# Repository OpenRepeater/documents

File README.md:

Welcome to the OpenRepeater Project.
=======

This is the main repository for the OpenRepeater Project where WIKIs and Issues live.

Please go to the OpenRepeater organization to see all the associated repositories with this project: https://github.com/OpenRepeater

PROJECT PAGE
https://Openrepeater.com

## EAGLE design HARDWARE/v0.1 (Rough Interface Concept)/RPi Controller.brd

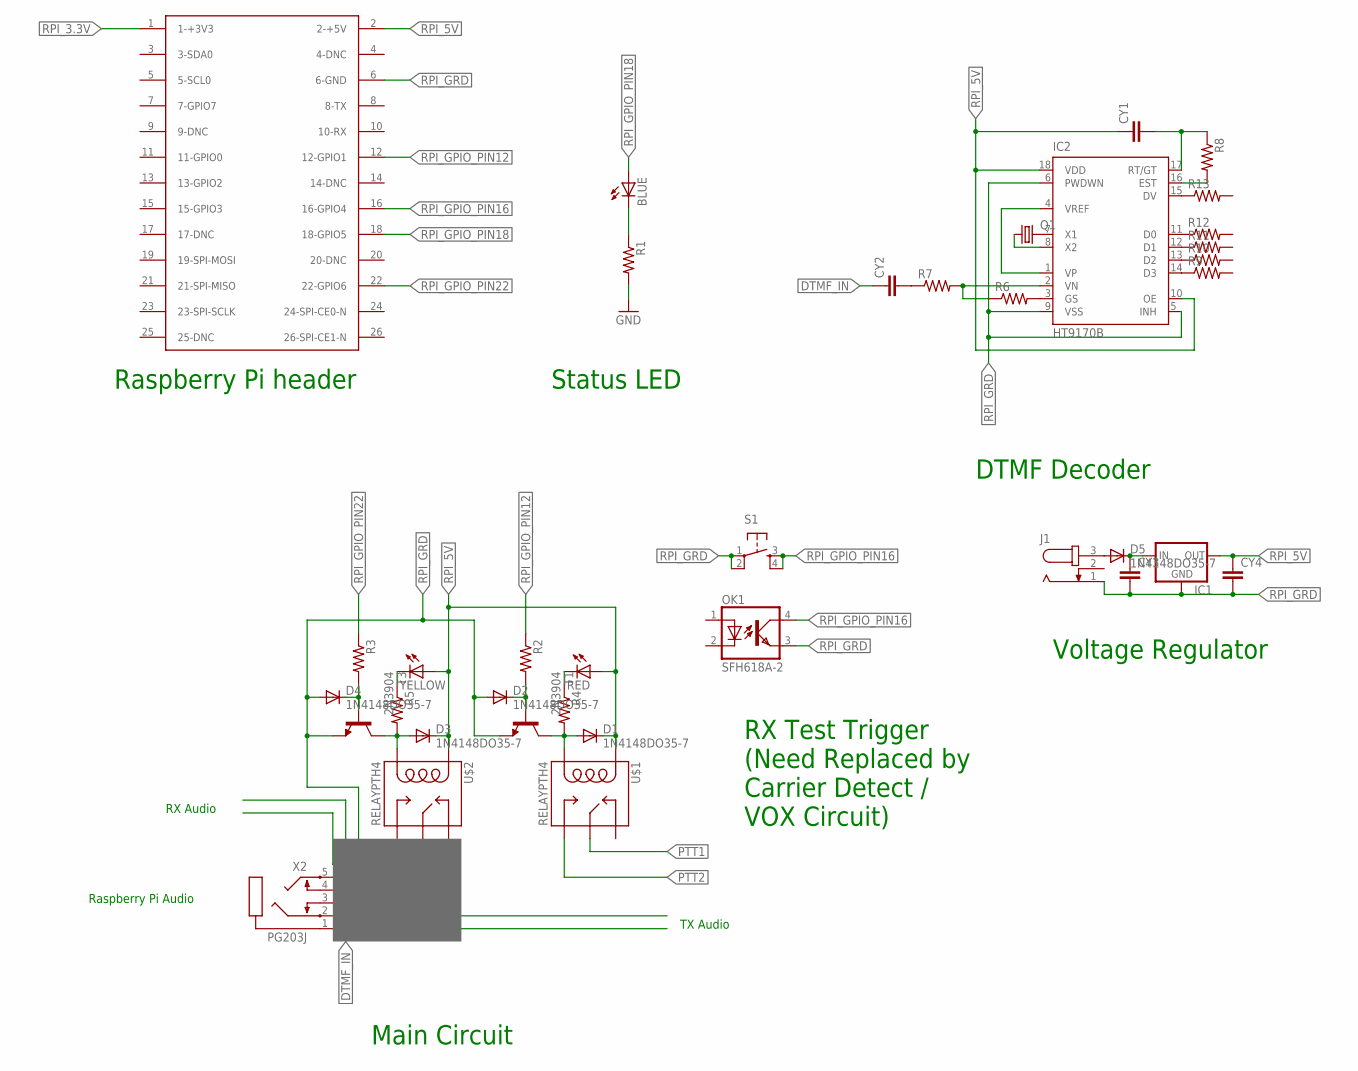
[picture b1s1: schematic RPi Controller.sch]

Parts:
BLUE: LED3MM
CY1, CY2, CY3, CY4: CYYC7B5; YC7B5
D1, D2, D3, D4, D5: 1N4148DO35-7; DO35-7
IC1: V_REG_78XX-TO-220; TO-220-ALT
IC2: HT9170B; DIL18
J1: JACK-PLUG0; SPC4077
OK1: SFH618A-2; DIP4
Q1: CRYSTALHC49U-V; HC49U-V
R1, R2, R3, R4, R5, R6, R7, R8, R9, R10, R11, R12, R13: R-US_0204/7; 0204/7
RED: LED3MM
S1: TAC_SWITCHPTH; TACTILE-PTH
T1, T3: 2N3904; TO92
U$1, U$2: RELAYPTH4; RELAY-JZC
X1: P1A; RASPBERRY-PI-HEADER
X2: PG203J
YELLOW: LED3MM

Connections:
DTMF_IN: CY2.1, U$2.4 (MAIN)
GND: R1.2
unnamed: BLUE.K (C), R1.1
unnamed: R4.1, RED.K (C)
unnamed: U$2.2 (NC), X2.5
unnamed: D2.C, R2.2, T1.2 (B)
unnamed: D1.A, R4.2, T1.1 (C), U$1.1 (COIL2)
unnamed: R5.1, YELLOW.K (C)
unnamed: IC2.7 (X1), Q1.2
unnamed: D4.C, R3.2, T3.2 (B)
unnamed: D3.A, R5.2, T3.1 (C), U$2.1 (COIL2)
unnamed: IC2.8 (X2), Q1.1
unnamed: IC2.14 (D3), R9.1
unnamed: IC2.2 (VN), R6.1, R7.2
unnamed: IC2.13 (D2), R10.1
unnamed: IC2.3 (GS), R6.2
unnamed: IC2.1 (VP), IC2.4 (VREF)
unnamed: IC2.12 (D1), R11.1
unnamed: IC2.11 (D0), R12.1
unnamed: IC2.15 (DV), R13.1
unnamed: CY3.1, D5.C, IC1.IN
unnamed: IC2.16 (EST), R8.2
unnamed: CY1.2, IC2.17 (RT/GT), R8.1
unnamed: CY2.2, R7.1
unnamed: D5.A, J1.3
PTT1: U$1.4 (MAIN)
PTT2: U$1.3 (NO)
RPI_3.3V: X1.1 (1-+3V3)
RPI_5V: CY1.1, CY4.1, D1.C, D3.C, IC1.OUT, IC2.10 (OE), IC2.18 (VDD), RED.A, U$1.5 (COIL1), U$2.5 (COIL1), X1.2 (2-+5V), YELLOW.A
RPI_GPIO_PIN12: R2.1, X1.12 (12-GPIO1)
RPI_GPIO_PIN16: OK1.4 (COL), S1.3, S1.4, X1.16 (16-GPIO4)
RPI_GPIO_PIN18: BLUE.A, X1.18 (18-GPIO5)
RPI_GPIO_PIN22: R3.1, X1.22 (22-GPIO6)
RPI_GRD: CY3.2, CY4.2, D2.A, D4.A, IC1.GND, IC2.5 (INH), IC2.6 (PWDWN), IC2.9 (VSS), J1.1, OK1.3 (EMIT), S1.1, S1.2, T1.3 (E), T3.3 (E), X1.6 (6-GND), X2.1

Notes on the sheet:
Raspberry Pi header
Status LED
Raspberry Pi Audio
RX Audio
TX Audio
DTMF Decoder
Voltage Regulator
Main Circuit
RX Test Trigger (Need Replaced by Carrier Detect / VOX Circuit)

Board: 2 copper layers, 37 parts (0 on the bottom side), 30 nets, no tracks yet.

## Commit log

2014-04-21 Read Me Update
    update to read me file
2014-04-24 Hardware Dir Test
2014-04-24 Initial Hardware Commit
2014-04-24 Upload BMP Image Autoraspi
    For study options.
2014-05-06 Added License File
2014-07-18 Create test.txt
    git test
2014-08-04 Remove unused filed
    move to another repository in organization
2014-08-05 Readme update
2014-09-12 Start of Branding Documentation
2014-11-27 Branding Updates
2014-11-28 Square Logo & Favicon
2014-11-28 favicon update
2015-12-12 Fix FF Issue
2015-12-12 Fix FF bug
2015-12-12 footer changes
2015-12-12 FF Bug Fix
2020-11-28 Upload SVG Files
2020-11-28 Add Affinity Designer Photos

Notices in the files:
parts and their libraries:
SparkFun-Electromechanical: Licensing: CC v3.0 Share-Alike You are welcome to use this library for commercial purposes.
